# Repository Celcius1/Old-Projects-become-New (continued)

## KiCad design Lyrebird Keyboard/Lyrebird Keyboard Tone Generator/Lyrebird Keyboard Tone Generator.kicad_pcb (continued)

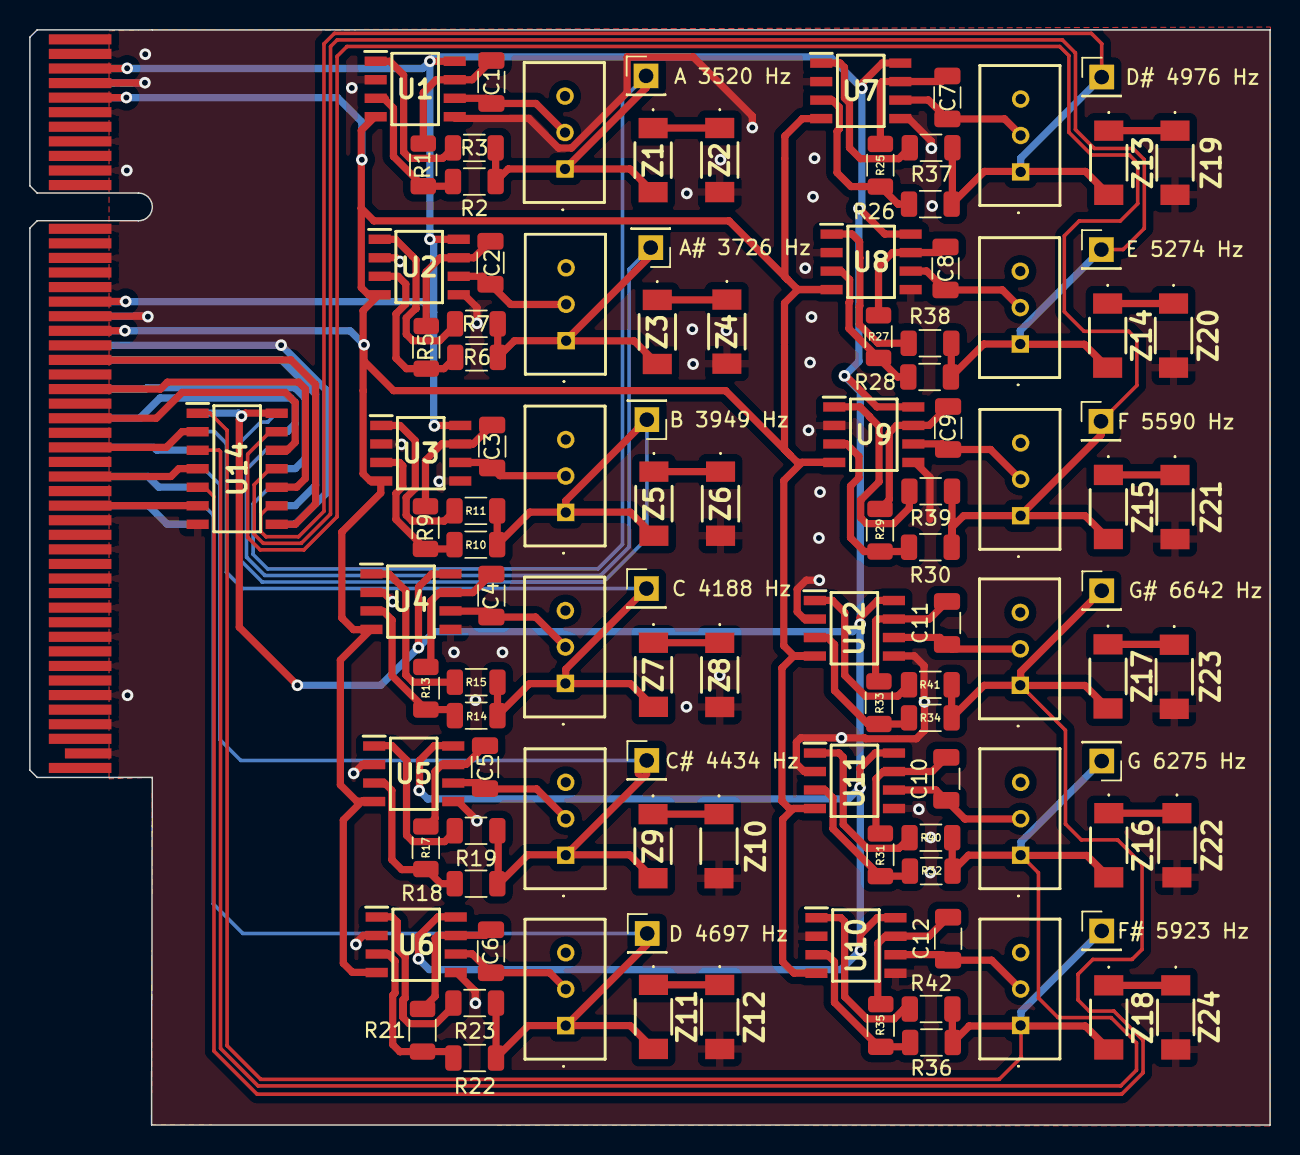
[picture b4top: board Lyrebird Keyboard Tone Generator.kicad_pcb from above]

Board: 2 copper layers, 85.1 x 75.2 mm, 111 parts (1 on the bottom side), 87 nets.

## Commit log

2023-10-03 First Upload
2023-10-07 Design of PSU so far
2023-10-07 Swapped out Op-Amp for a Comparator
2023-10-07 Minor Change to feedback circuit
2023-10-08 A few minor changes
2023-12-06 Lyrebird Initial Upload
2023-12-07 additional tracks laid
2023-12-08 Added schematic definitions
2023-12-09 Tracks almost finished
2023-12-10 Mainboard Complete
2023-12-10 Working on Tone Generator
2023-12-11 Further Tone Generator Work, Diode mixers placed
2023-12-12 Major Design Changes
    Completed Tone Generator Board, board now only provides base notes, individual notes will be generated on the wave shaping boards.
    Made major changes to pci slot config, and have increased grounding of the slots.
    May need decoupling capacitors on tone generator board, but tight for room
2023-12-12 Mainboard Changes
    Adjusted mainboard, the longer PCI slots are now instrument slots not wave shaper slots, and slot 4 in the longer is also able to support midi implementation
2023-12-13 Piano Board Layout
    Started doing circuit that creates the piano sound.
2023-12-15 Design Changes
    Fix a number of symbol issues, and connection faults
2023-12-16 Schematic Updates
    Made updates to schematics, to use correct symbols, and minor PCB updates, further work on the piano card design
2023-12-18 Move PSU and Amp off of mainboard
    Moved Power Supply to its own board, single layer. Moved Class D amp onto a daughter board, modifiying to also have a 1/4" balanced output as well as amplified output
2023-12-20 Added KiCAD library
    Uploaded current ECAD library, to facilitate editing away from main work computer
